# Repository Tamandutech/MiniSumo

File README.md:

# MiniSumo
This project contains all files from our MiniSumo Robot
<br/>

# Contact Us
Pedro Gabriel Gengo Lourenço  - pedro.gabriel.lourenco@hotmail.com 
<br/>
Henrique Zanferrari Hadermeck - henriquezanferrari@gmail.com
<br/>
Karoliny Anjos - karolinyanjos@outlook.com

# PCB
Bottom
<br/>

<br/>
Top
<br/>

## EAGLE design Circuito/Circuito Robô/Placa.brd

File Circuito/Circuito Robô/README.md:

<b>MiniSumo Project</b>
<br>
This repository contains all files, designs and codes used for built MiniSumo of Tamandutech.
<br>
<br>
<b>Contacts</b>
<br>
Pedro Gabriel Gengo Lourenço  - pedro.gabriel.lourenco@hotmail.com
<br>
Henrique Zanferrari Hadermeck - henriquezanferrari@gmail.com

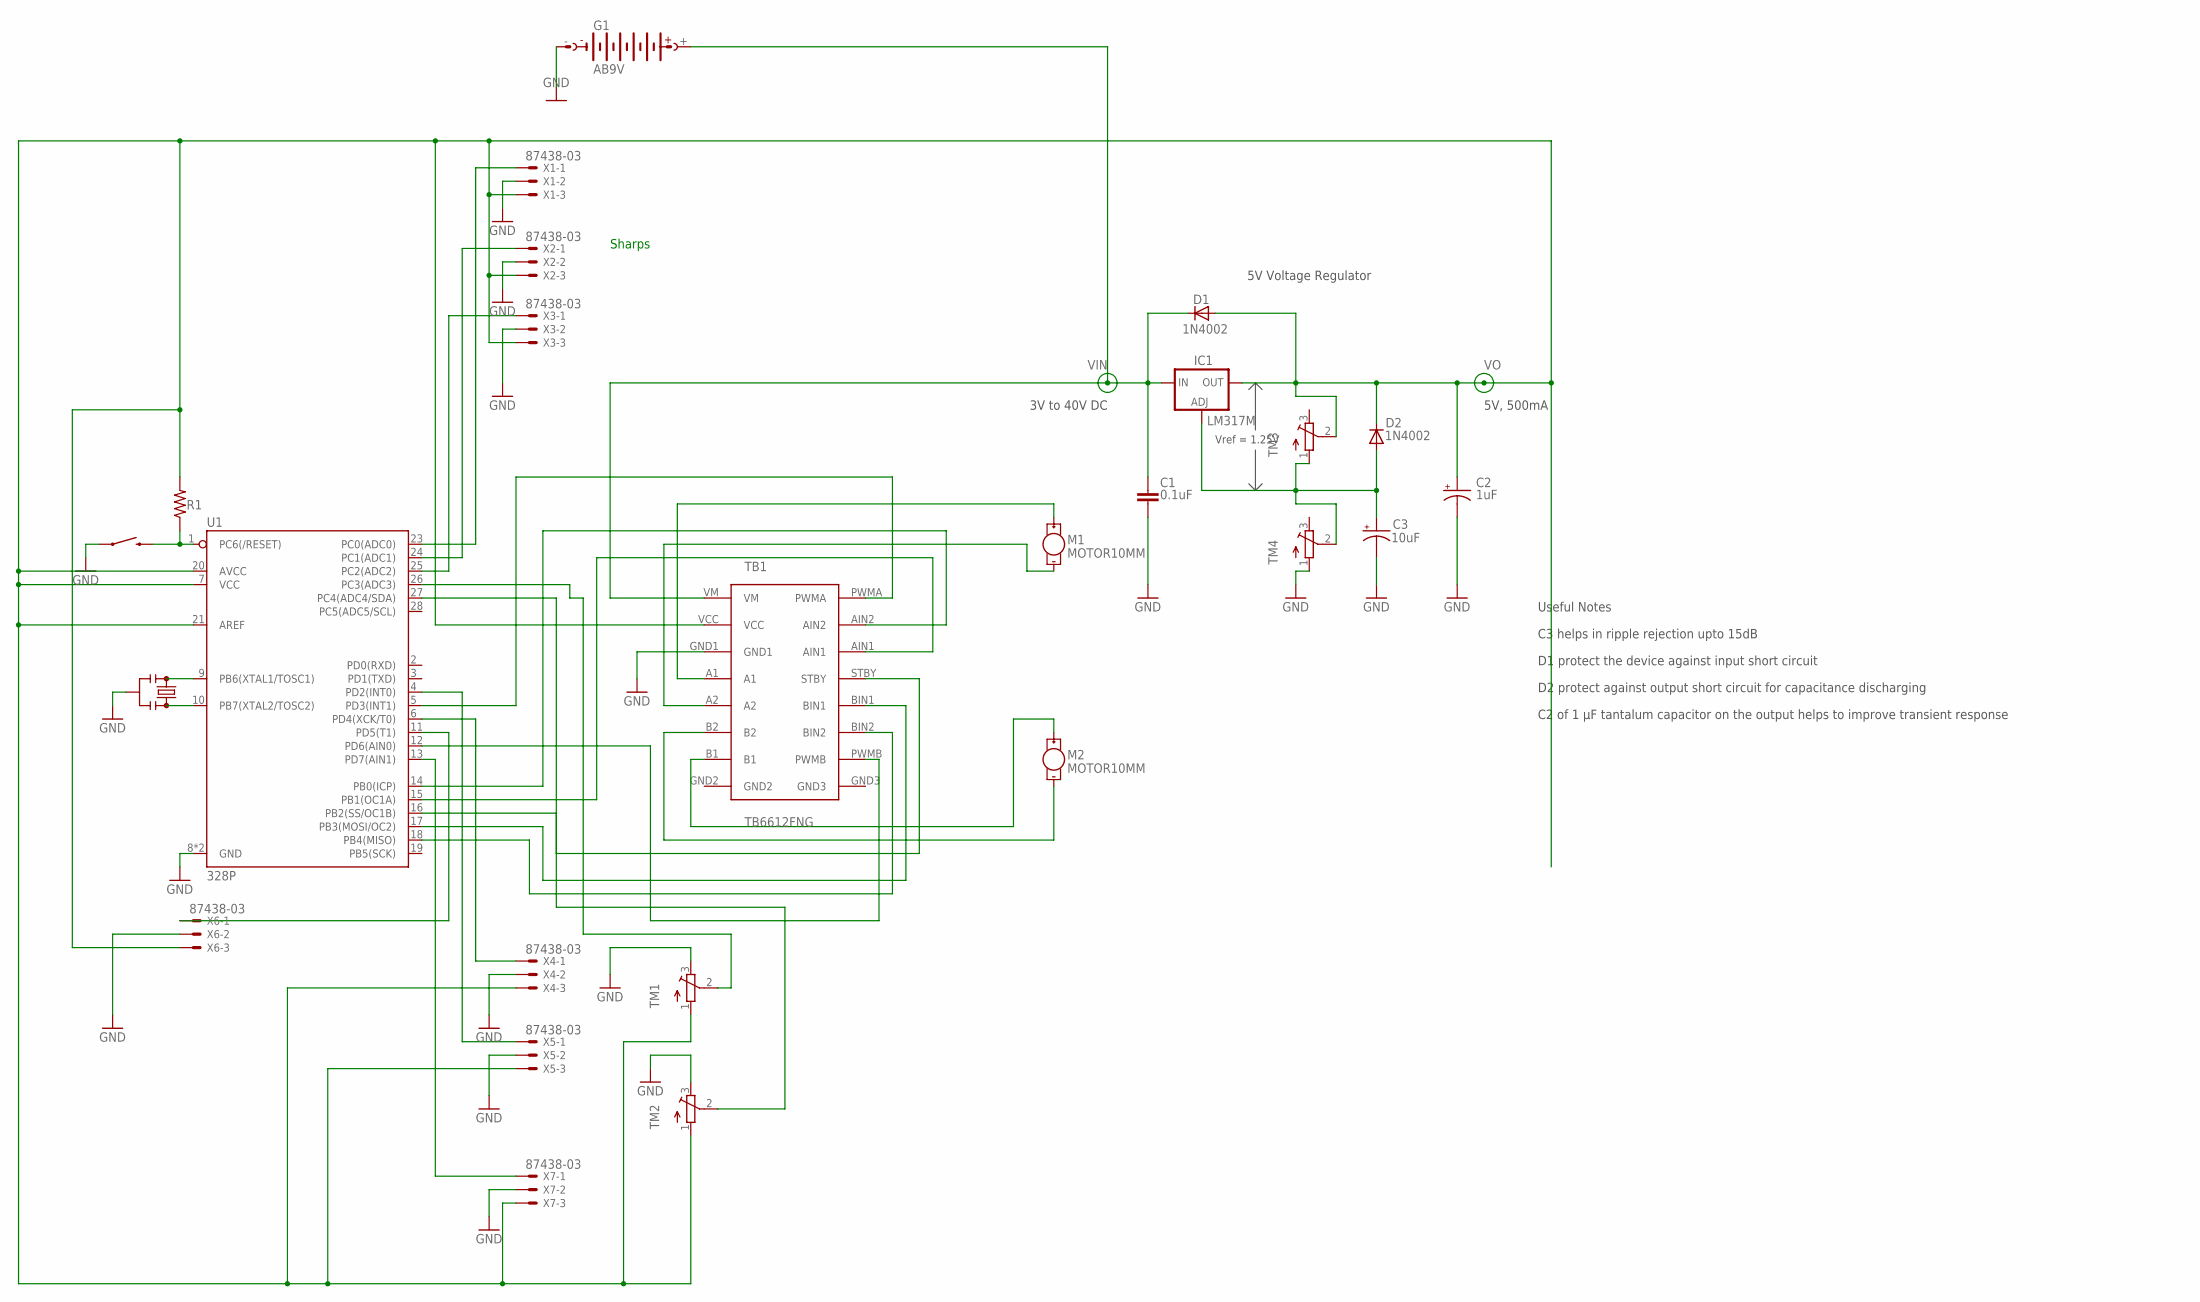
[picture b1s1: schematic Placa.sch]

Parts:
C1: 0.1uF; C075-052X106
C2: 1uF; 085CS_1AR
C3: 10uF; 085CS_1AR
D1, D2: 1N4002; DO41-10
G1: AB9V
IC1: LM317MBSTT3; SOT223; PARTNUMBER LM317M
M1, M2: MOTOR10MM; VIBE-MOTOR-10MM
R1: R-US_0204/7; 0204/7
S1: MOMENTARY-SWITCH-SPST-SMD-6.2MM-TALL; TACTILE_SWITCH_SMD_6.2MM_TALL
TB1: TB6612FNG
TM1, TM2, TM3, TM4: TRIMPOT3386; TRIM-3386
U1: 328P; DIP28
X1, X2, X3, X4, X5, X6, X7: 87438-03
Y1: 16MHz; RESONATOR-SMD-3.2X1.3

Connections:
GND: C1.2, C2.-, C3.-, G1.-, S1.A2 (1), TB1.GND1, TM1.3 (E), TM2.3 (E), TM4.1 (A), U1.8 (GND), U1.22 (GND), X1.2, X2.2, X3.2, X4.2, X5.2, X6.2, X7.2, Y1.2
unnamed: U1.9 (PB6(XTAL1/TOSC1)), Y1.1
unnamed: U1.10 (PB7(XTAL2/TOSC2)), Y1.3
unnamed: R1.1, S1.B2 (2), U1.1 (PC6(/RESET))
unnamed: TB1.AIN2, U1.14 (PB0(ICP))
unnamed: TB1.AIN1, U1.15 (PB1(OC1A))
unnamed: M1.+, TB1.A1
unnamed: M1.-, TB1.A2
unnamed: M2.-, TB1.B2
unnamed: M2.+, TB1.B1
unnamed: TB1.PWMA, U1.5 (PD3(INT1))
unnamed: TB1.STBY, U1.16 (PB2(SS/OC1B))
unnamed: TB1.BIN1, U1.17 (PB3(MOSI/OC2))
unnamed: C3.+, D2.A, IC1.1 (ADJ), TM3.1 (A), TM4.2 (S)
unnamed: U1.23 (PC0(ADC0)), X1.1
unnamed: U1.24 (PC1(ADC1)), X2.1
unnamed: U1.25 (PC2(ADC2)), X3.1
unnamed: U1.4 (PD2(INT0)), X5.1
unnamed: U1.13 (PD7(AIN1)), X7.1
unnamed: U1.11 (PD5(T1)), X6.1
unnamed: U1.6 (PD4(XCK/T0)), X4.1
unnamed: TB1.BIN2, U1.18 (PB4(MISO))
unnamed: TB1.PWMB, U1.12 (PD6(AIN0))
unnamed: TM2.2 (S), U1.27 (PC4(ADC4/SDA))
unnamed: TM1.2 (S), U1.26 (PC3(ADC3))
VIN: C1.1, D1.C, G1.+, IC1.3 (IN), TB1.VM
VO: C2.+, D1.A, D2.C, IC1.4 (OUT), R1.2, TB1.VCC, TM1.1 (A), TM2.1 (A), TM3.2 (S), U1.7 (VCC), U1.20 (AVCC), U1.21 (AREF), X1.3, X2.3, X3.3, X4.3, X5.3, X6.3, X7.3

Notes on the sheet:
5V Voltage Regulator
C3 helps in ripple rejection upto 15dB
D1 protect the device against input short circuit
D2 protect against output short circuit for capacitance discharging
C2 of 1 µF tantalum capacitor on the output helps to improve transient response
Useful Notes
5V, 500mA
3V to 40V DC
Vref = 1.25V
Sharps

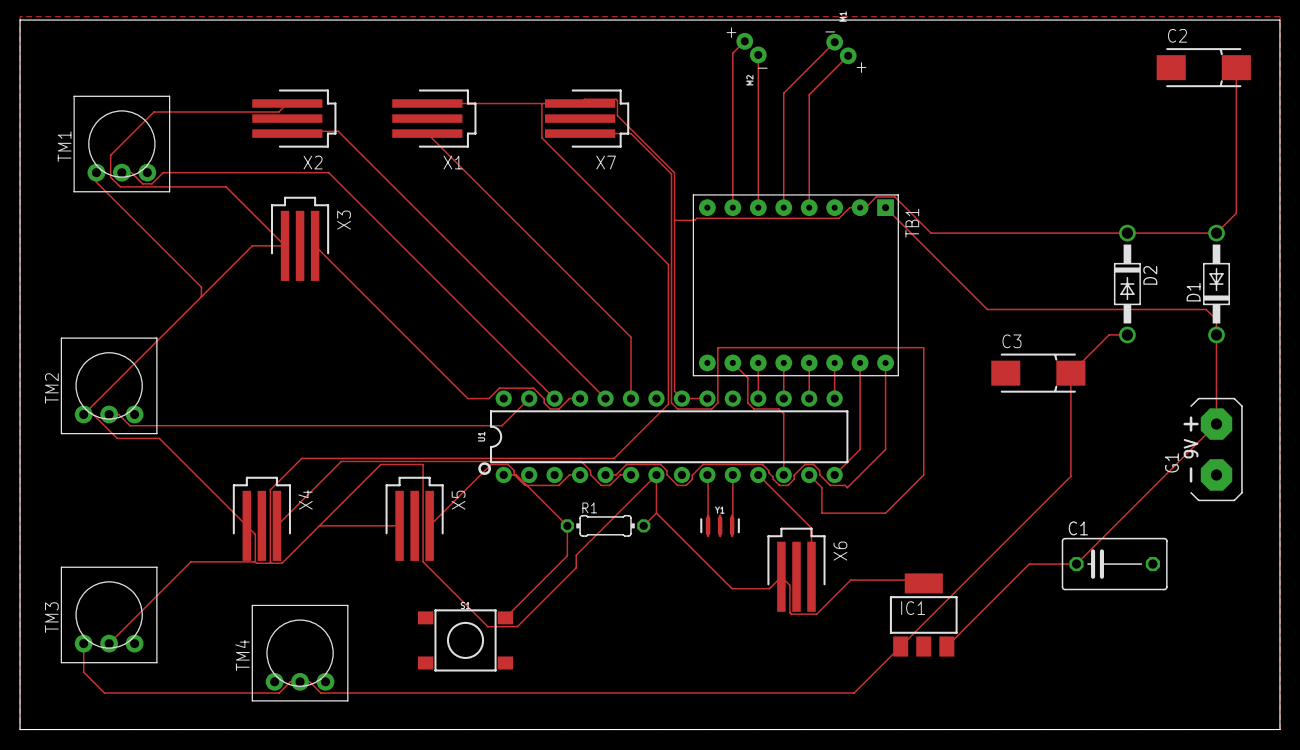
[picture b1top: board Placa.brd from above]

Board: 2 copper layers, 125.7 x 70.8 mm, 25 parts (0 on the bottom side), 27 nets.

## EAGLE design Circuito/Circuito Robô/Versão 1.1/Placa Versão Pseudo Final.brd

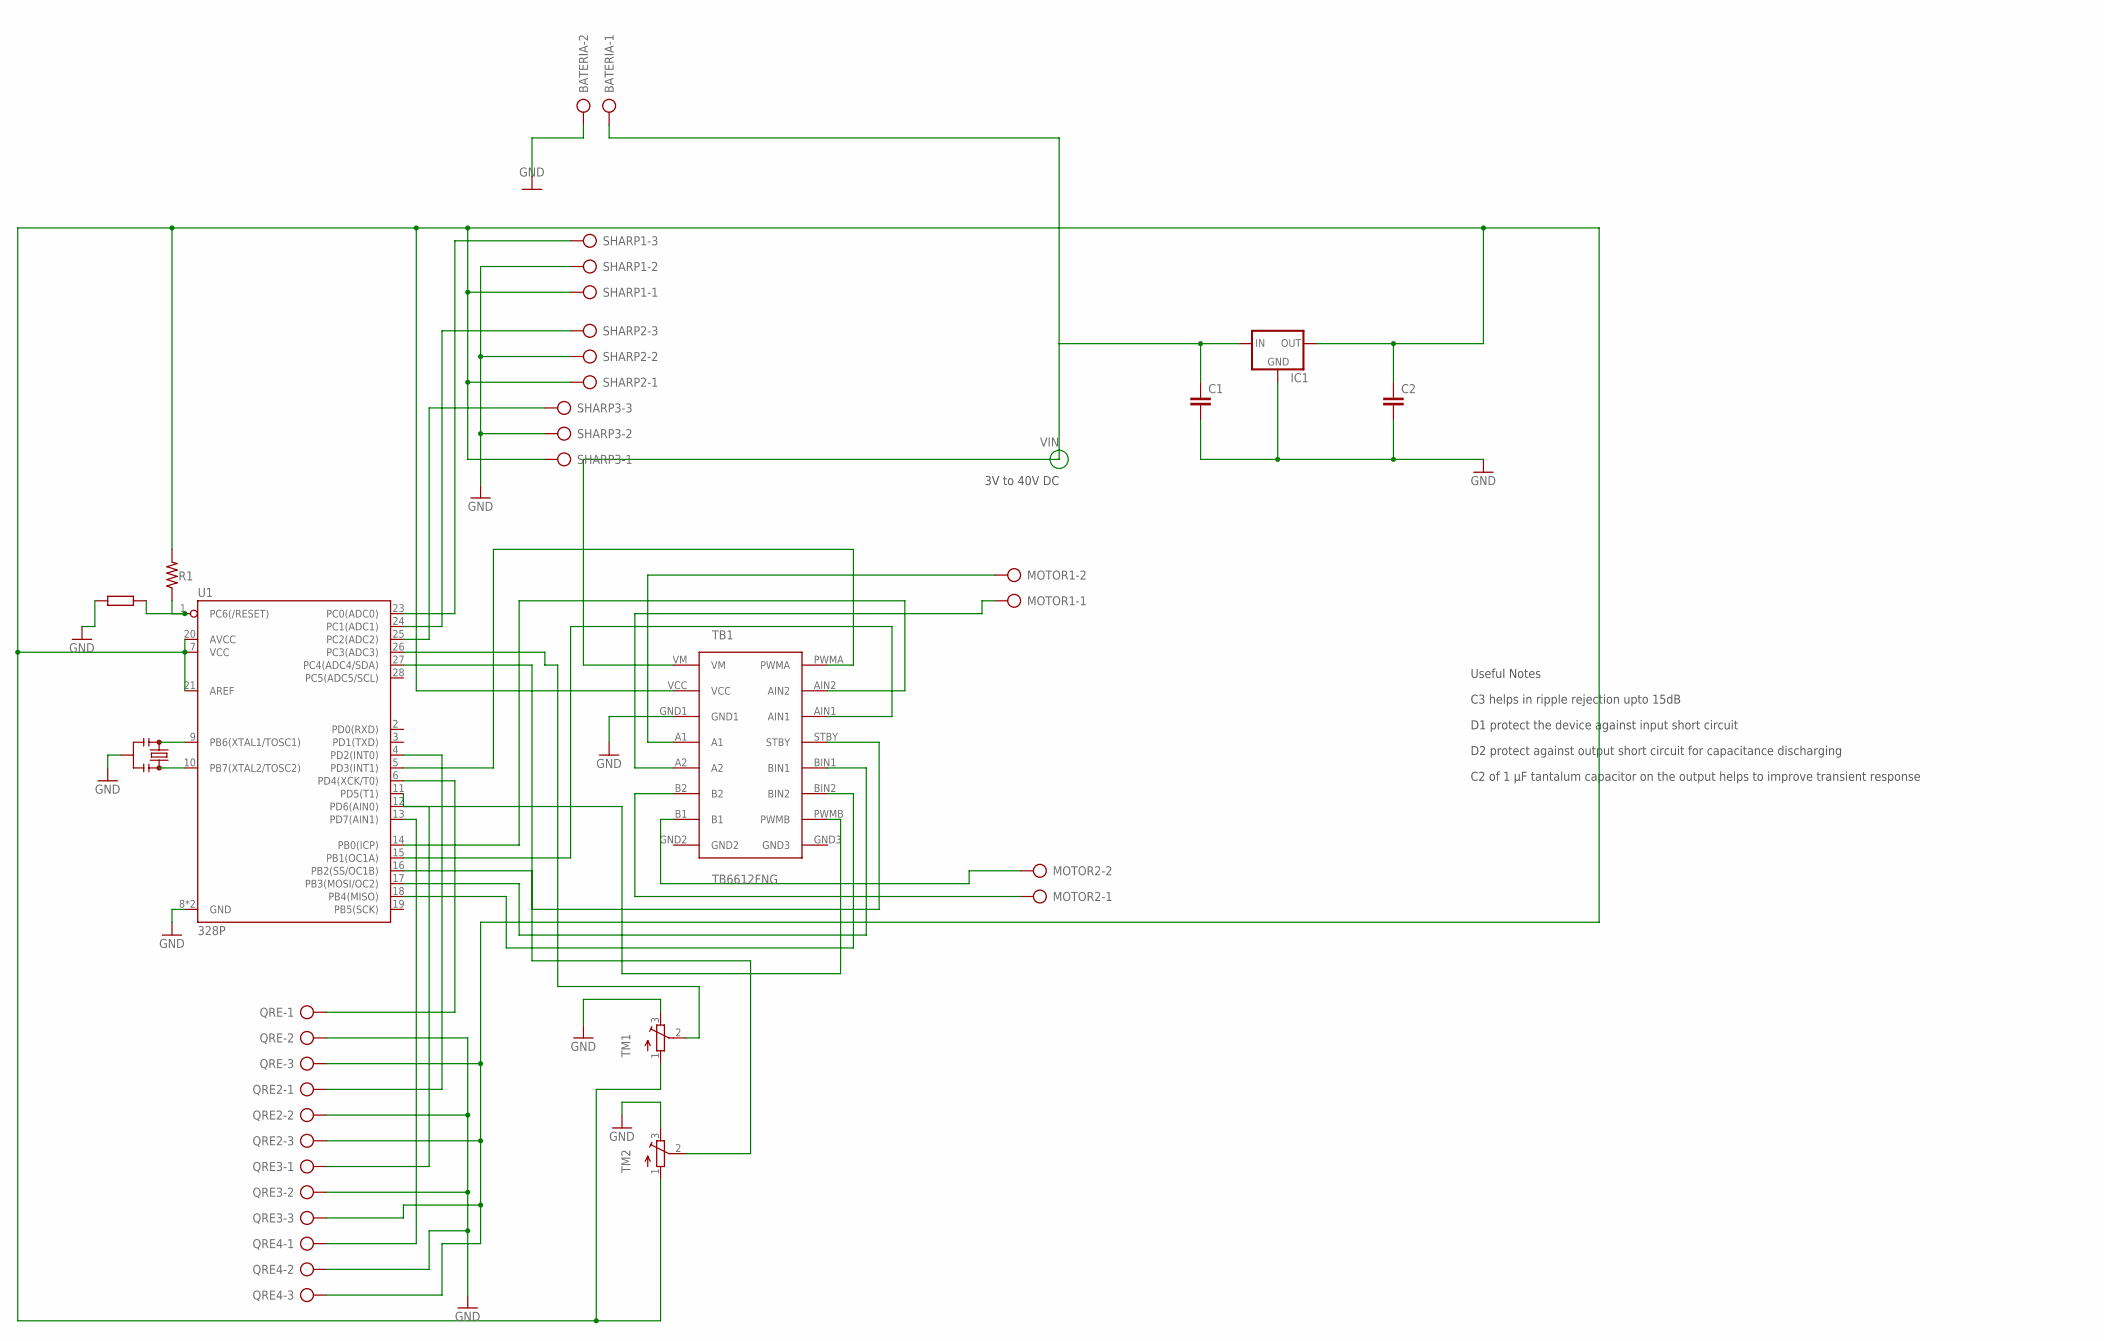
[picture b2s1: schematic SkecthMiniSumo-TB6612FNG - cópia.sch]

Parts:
BATERIA: AK500/2-H
C1, C2: C5/3; C5B3
IC1: 78LXX
MOTOR1, MOTOR2: AK500/2-H
QRE, QRE2, QRE3, QRE4: AK500/3-H
R1: R-US_0204/7; 0204/7
SHARP1, SHARP2, SHARP3: AK500/3-H
TB1: TB6612FNG
TM1, TM2: TRIMPOT3386; TRIM-3386
U1: 328P; DIP28
Y1: 16MHz; RESONATOR-SMD-3.2X1.3

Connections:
GND: BATERIA.2, C1.2, C2.2, IC1.GND, QRE.2, QRE2.2, QRE3.2, QRE4.2, SHARP1.2, SHARP2.2, SHARP3.2, TB1.GND1, TM1.3 (E), TM2.3 (E), U1.8 (GND), U1.22 (GND), Y1.2
unnamed: U1.9 (PB6(XTAL1/TOSC1)), Y1.1
unnamed: U1.10 (PB7(XTAL2/TOSC2)), Y1.3
unnamed: R1.1, U1.1 (PC6(/RESET))
unnamed: TB1.AIN2, U1.14 (PB0(ICP))
unnamed: TB1.AIN1, U1.15 (PB1(OC1A))
unnamed: MOTOR1.2, TB1.A1
unnamed: MOTOR1.1, TB1.A2
unnamed: MOTOR2.1, TB1.B2
unnamed: MOTOR2.2, TB1.B1
unnamed: TB1.PWMA, U1.5 (PD3(INT1))
unnamed: TB1.STBY, U1.16 (PB2(SS/OC1B))
unnamed: TB1.BIN1, U1.17 (PB3(MOSI/OC2))
unnamed: SHARP1.3, U1.23 (PC0(ADC0))
unnamed: SHARP2.3, U1.24 (PC1(ADC1))
unnamed: SHARP3.3, U1.25 (PC2(ADC2))
unnamed: QRE2.1, U1.4 (PD2(INT0))
unnamed: QRE4.1, U1.13 (PD7(AIN1))
unnamed: QRE3.1, U1.12 (PD6(AIN0))
unnamed: QRE.1, U1.6 (PD4(XCK/T0))
unnamed: TB1.BIN2, U1.18 (PB4(MISO))
unnamed: TB1.PWMB, U1.11 (PD5(T1))
unnamed: TM2.2 (S), U1.27 (PC4(ADC4/SDA))
unnamed: TM1.2 (S), U1.26 (PC3(ADC3))
VIN: BATERIA.1, C1.1, IC1.IN, TB1.VM
VO: C2.1, IC1.OUT, QRE.3, QRE2.3, QRE3.3, QRE4.3, R1.2, SHARP1.1, SHARP2.1, SHARP3.1, TB1.VCC, TM1.1 (A), TM2.1 (A), U1.7 (VCC), U1.20 (AVCC), U1.21 (AREF)

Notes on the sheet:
C3 helps in ripple rejection upto 15dB
D1 protect the device against input short circuit
D2 protect against output short circuit for capacitance discharging
C2 of 1 µF tantalum capacitor on the output helps to improve transient response
Useful Notes
3V to 40V DC

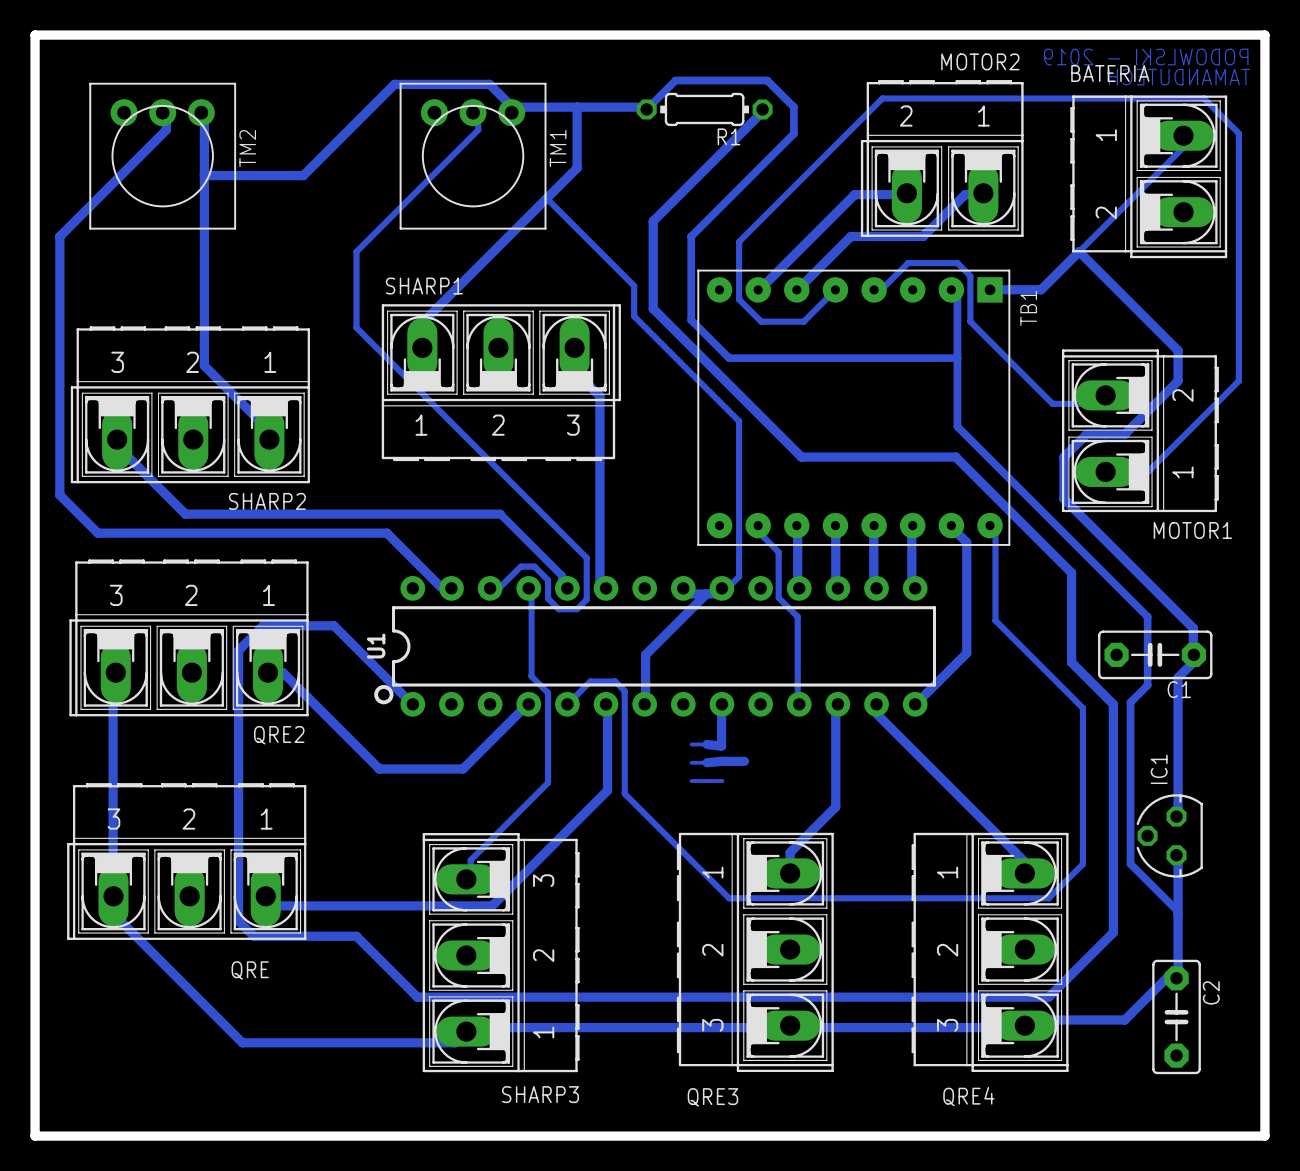
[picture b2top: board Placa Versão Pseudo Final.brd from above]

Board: 2 copper layers, 80.8 x 72.4 mm, 19 parts (1 on the bottom side), 26 nets.

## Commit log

2018-12-27 Recover
2018-12-27 Change on paths
2018-12-27 Changing folder structure
2018-12-27 Changing files structure
2019-01-05 Conectores e Trimpots
2019-01-07 Adiciona TB6612 e Trimpots
2019-01-08 PCB com 125mm
2019-01-08 Placa com 125mm
2019-01-27 PCB with routes
2019-01-27 PCB Images
2019-01-29 Routes update
2019-02-27 Versão pós Luan
2019-02-28 Placa pseudo pronta

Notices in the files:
parts and their libraries:
SparkFun-Electromechanical: Licensing: Creative Commons ShareAlike 4.0 International - https://creativecommons.org/licenses/by-sa/4.0
